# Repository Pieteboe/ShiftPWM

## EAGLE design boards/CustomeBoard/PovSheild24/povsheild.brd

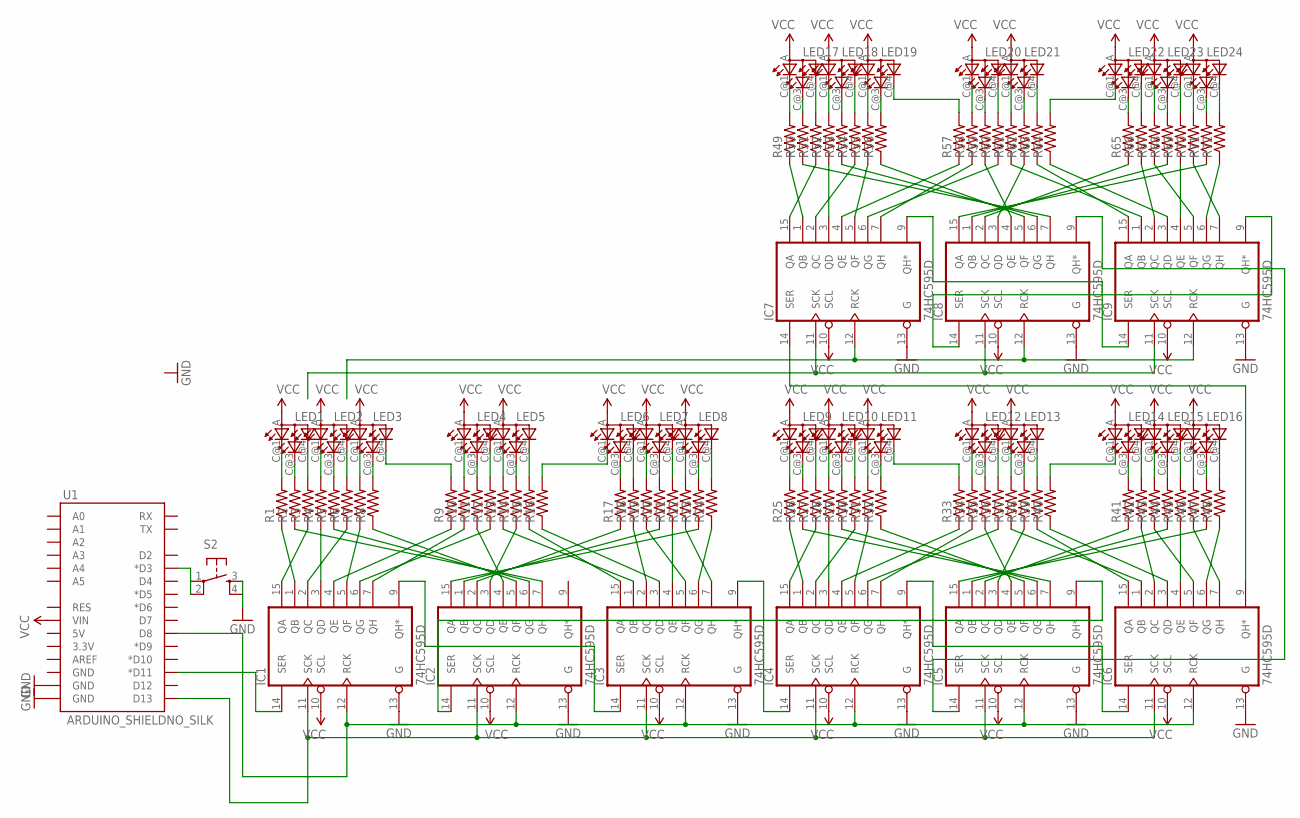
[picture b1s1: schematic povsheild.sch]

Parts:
IC1, IC2, IC3, IC4, IC5, IC6, IC7, IC8, IC9: 74HC595D; SO16
LED1, LED2, LED3, LED4, LED5, LED6, LED7, LED8, LED9, LED10, LED11, LED12, LED13, LED14, LED15, LED16, LED17, LED18, LED19, LED20, LED21, LED22, LED23, LED24: TOPLED-3P-LCC-4; P-LCC-4
R1, R2, R3, R4, R5, R6, R7, R8, R9, R10, R11, R12, R13, R14, R15, R16, R17, R18, R19, R20, R21, R22, R23, R24, R25, R26, R27, R28, R29, R30, R31, R32, R33, R34, R35, R36, R37, R38, R39, R40, R41, R42, R43, R44, R45, R46, R47, R48, R49, R50, R51, R52, R53, R54, R55, R56, R57, R58, R59, R60, R61, R62, R63, R64, R65, R66, R67, R68, R69, R70, R71, R72: RESISTOR0805-RES; 0805
S2: TAC_SWITCHSMD; TACTILE_SWITCH_SMD
U1: ARDUINO_SHIELDNO_SILK; DUEMILANOVE_VIAS

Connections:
GND: IC1.8 (GND), IC1.13 (G), IC2.8 (GND), IC2.13 (G), IC3.8 (GND), IC3.13 (G), IC4.8 (GND), IC4.13 (G), IC5.8 (GND), IC5.13 (G), IC6.8 (GND), IC6.13 (G), IC7.8 (GND), IC7.13 (G), IC8.8 (GND), IC8.13 (G), IC9.8 (GND), IC9.13 (G), S2.3, S2.4, U1.GND@0 (GND), U1.GND@1 (GND)
LATCH: IC1.12 (RCK), IC2.12 (RCK), IC3.12 (RCK), IC4.12 (RCK), IC5.12 (RCK), IC6.12 (RCK), IC7.12 (RCK), IC8.12 (RCK), IC9.12 (RCK), U1.D8
unnamed: IC1.15 (QA), R3.1
unnamed: IC1.1 (QB), R1.1
unnamed: IC1.2 (QC), R6.1
unnamed: IC1.3 (QD), R4.1
unnamed: IC1.4 (QE), R9.1
unnamed: IC1.5 (QF), R7.1
unnamed: IC1.6 (QG), R12.1
unnamed: IC1.7 (QH), R10.1
unnamed: LED1.C@1 (CRED), R1.2
unnamed: LED1.C@3 (CBLUE), R2.2
unnamed: LED1.C@4 (CGREEN), R3.2
unnamed: LED2.C@1 (CRED), R4.2
unnamed: LED2.C@3 (CBLUE), R5.2
unnamed: LED2.C@4 (CGREEN), R6.2
unnamed: LED3.C@1 (CRED), R7.2
unnamed: LED3.C@3 (CBLUE), R8.2
unnamed: LED3.C@4 (CGREEN), R9.2
unnamed: LED4.C@1 (CRED), R10.2
unnamed: IC3.15 (QA), R15.1
unnamed: IC3.1 (QB), R13.1
unnamed: LED4.C@3 (CBLUE), R11.2
unnamed: IC3.2 (QC), R18.1
unnamed: IC3.3 (QD), R16.1
unnamed: IC3.4 (QE), R21.1
unnamed: IC3.5 (QF), R19.1
unnamed: IC3.6 (QG), R24.1
unnamed: IC3.7 (QH), R22.1
unnamed: LED4.C@4 (CGREEN), R12.2
unnamed: LED5.C@1 (CRED), R13.2
unnamed: LED5.C@3 (CBLUE), R14.2
unnamed: LED5.C@4 (CGREEN), R15.2
unnamed: LED6.C@1 (CRED), R16.2
unnamed: LED6.C@3 (CBLUE), R17.2
unnamed: LED6.C@4 (CGREEN), R18.2
unnamed: IC2.15 (QA), R23.1
unnamed: IC2.1 (QB), R20.1
unnamed: LED7.C@1 (CRED), R19.2
unnamed: IC2.2 (QC), R17.1
unnamed: LED7.C@3 (CBLUE), R20.2
unnamed: IC2.3 (QD), R14.1
unnamed: LED7.C@4 (CGREEN), R21.2
unnamed: IC2.4 (QE), R11.1
unnamed: IC2.5 (QF), R8.1
unnamed: IC2.6 (QG), R5.1
unnamed: IC2.7 (QH), R2.1
unnamed: LED8.C@1 (CRED), R22.2
unnamed: LED8.C@3 (CBLUE), R23.2
unnamed: LED8.C@4 (CGREEN), R24.2
unnamed: IC4.15 (QA), R27.1
unnamed: IC4.1 (QB), R25.1
unnamed: IC4.2 (QC), R30.1
unnamed: IC4.3 (QD), R28.1
unnamed: IC4.4 (QE), R33.1
unnamed: IC4.5 (QF), R31.1
unnamed: IC4.6 (QG), R36.1
unnamed: IC4.7 (QH), R34.1
unnamed: LED9.C@1 (CRED), R25.2
unnamed: LED9.C@3 (CBLUE), R26.2
unnamed: LED9.C@4 (CGREEN), R27.2
unnamed: LED10.C@1 (CRED), R28.2
unnamed: LED10.C@3 (CBLUE), R29.2
unnamed: LED10.C@4 (CGREEN), R30.2
unnamed: LED11.C@1 (CRED), R31.2
unnamed: LED11.C@3 (CBLUE), R32.2
unnamed: LED11.C@4 (CGREEN), R33.2
unnamed: LED12.C@1 (CRED), R34.2
unnamed: IC5.15 (QA), R47.1
unnamed: IC5.1 (QB), R44.1
unnamed: LED12.C@3 (CBLUE), R35.2
unnamed: IC5.2 (QC), R41.1
unnamed: IC5.3 (QD), R38.1
unnamed: IC5.4 (QE), R35.1
unnamed: IC5.5 (QF), R32.1
unnamed: IC5.6 (QG), R29.1
unnamed: IC5.7 (QH), R26.1
unnamed: LED12.C@4 (CGREEN), R36.2
unnamed: LED13.C@1 (CRED), R37.2
unnamed: LED13.C@3 (CBLUE), R38.2
unnamed: LED13.C@4 (CGREEN), R39.2
unnamed: LED14.C@1 (CRED), R40.2
unnamed: LED14.C@3 (CBLUE), R41.2
unnamed: LED14.C@4 (CGREEN), R42.2
unnamed: IC6.15 (QA), R39.1
unnamed: IC6.1 (QB), R37.1
unnamed: LED15.C@1 (CRED), R43.2
unnamed: IC6.2 (QC), R42.1
unnamed: LED15.C@3 (CBLUE), R44.2
unnamed: IC6.3 (QD), R40.1
unnamed: LED15.C@4 (CGREEN), R45.2
unnamed: IC6.4 (QE), R45.1
unnamed: IC6.5 (QF), R43.1
unnamed: IC6.6 (QG), R48.1
unnamed: IC6.7 (QH), R46.1
unnamed: LED16.C@1 (CRED), R46.2
unnamed: LED16.C@3 (CBLUE), R47.2
unnamed: LED16.C@4 (CGREEN), R48.2
unnamed: LED17.C@1 (CRED), R49.2
unnamed: LED17.C@3 (CBLUE), R50.2
unnamed: LED17.C@4 (CGREEN), R51.2
unnamed: LED18.C@1 (CRED), R52.2
unnamed: LED18.C@3 (CBLUE), R53.2
unnamed: LED18.C@4 (CGREEN), R54.2
unnamed: LED19.C@1 (CRED), R55.2
unnamed: LED19.C@3 (CBLUE), R56.2
unnamed: LED19.C@4 (CGREEN), R57.2
unnamed: LED20.C@1 (CRED), R58.2
unnamed: LED20.C@3 (CBLUE), R59.2
unnamed: LED20.C@4 (CGREEN), R60.2
unnamed: LED21.C@1 (CRED), R61.2
unnamed: LED21.C@3 (CBLUE), R62.2
unnamed: LED21.C@4 (CGREEN), R63.2
unnamed: LED22.C@1 (CRED), R64.2
unnamed: LED22.C@3 (CBLUE), R65.2
unnamed: LED22.C@4 (CGREEN), R66.2
unnamed: LED23.C@1 (CRED), R67.2
unnamed: LED23.C@3 (CBLUE), R68.2
unnamed: LED23.C@4 (CGREEN), R69.2
unnamed: LED24.C@1 (CRED), R70.2
unnamed: LED24.C@3 (CBLUE), R71.2
unnamed: LED24.C@4 (CGREEN), R72.2
unnamed: IC7.15 (QA), R51.1
unnamed: IC7.1 (QB), R49.1
unnamed: IC7.2 (QC), R54.1
unnamed: IC7.3 (QD), R52.1
unnamed: IC7.4 (QE), R57.1
unnamed: IC7.5 (QF), R55.1
unnamed: IC7.6 (QG), R60.1
unnamed: IC7.7 (QH), R58.1
unnamed: IC8.15 (QA), R71.1
unnamed: IC8.1 (QB), R68.1
unnamed: IC8.2 (QC), R65.1
unnamed: IC8.3 (QD), R62.1
unnamed: IC8.4 (QE), R59.1
unnamed: IC8.5 (QF), R56.1
unnamed: IC8.6 (QG), R53.1
unnamed: IC8.7 (QH), R50.1
unnamed: IC9.15 (QA), R63.1
unnamed: IC9.1 (QB), R61.1
unnamed: IC9.2 (QC), R66.1
unnamed: IC9.3 (QD), R64.1
unnamed: IC9.4 (QE), R69.1
unnamed: IC9.5 (QF), R67.1
unnamed: IC9.6 (QG), R72.1
unnamed: IC9.7 (QH), R70.1
unnamed: IC1.9 (QH*), IC3.14 (SER)
unnamed: IC3.9 (QH*), IC4.14 (SER)
unnamed: IC4.9 (QH*), IC6.14 (SER)
unnamed: IC6.9 (QH*), IC7.14 (SER)
unnamed: IC7.9 (QH*), IC9.14 (SER)
unnamed: IC2.14 (SER), IC5.9 (QH*)
unnamed: IC5.14 (SER), IC8.9 (QH*)
unnamed: IC8.14 (SER), IC9.9 (QH*)
unnamed: IC1.14 (SER), U1.D11 (*D11)
unnamed: S2.1, S2.2, U1.D3 (*D3)
SCK: IC1.11 (SCK), IC2.11 (SCK), IC3.11 (SCK), IC4.11 (SCK), IC5.11 (SCK), IC6.11 (SCK), IC7.11 (SCK), IC8.11 (SCK), IC9.11 (SCK), U1.D13
VCC: IC1.10 (SCL), IC1.16 (VCC), IC2.10 (SCL), IC2.16 (VCC), IC3.10 (SCL), IC3.16 (VCC), IC4.10 (SCL), IC4.16 (VCC), IC5.10 (SCL), IC5.16 (VCC), IC6.10 (SCL), IC6.16 (VCC), IC7.10 (SCL), IC7.16 (VCC), IC8.10 (SCL), IC8.16 (VCC), IC9.10 (SCL), IC9.16 (VCC), LED1.A (A2), LED2.A (A2), LED3.A (A2), LED4.A (A2), LED5.A (A2), LED6.A (A2), LED7.A (A2), LED8.A (A2), LED9.A (A2), LED10.A (A2), LED11.A (A2), LED12.A (A2), LED13.A (A2), LED14.A (A2), LED15.A (A2), LED16.A (A2), LED17.A (A2), LED18.A (A2), LED19.A (A2), LED20.A (A2), LED21.A (A2), LED22.A (A2), LED23.A (A2), LED24.A (A2), U1.VIN

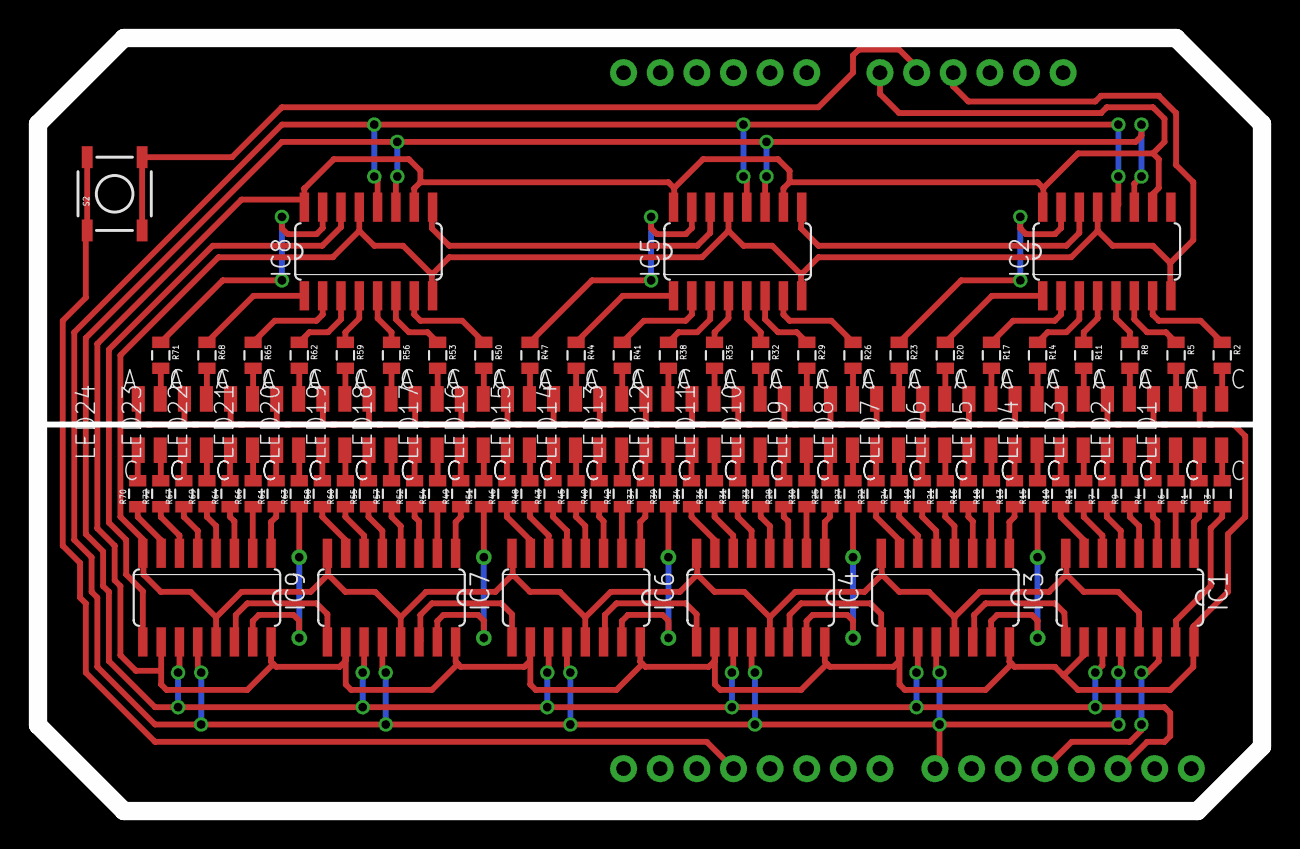
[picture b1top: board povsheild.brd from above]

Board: 2 copper layers, 84.9 x 53.6 mm, 107 parts (0 on the bottom side), 158 nets.

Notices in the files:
parts and their libraries:
SparkFun-Resistors: Licensing: Creative Commons ShareAlike 4.0 International - https://creativecommons.org/licenses/by-sa/4.0
